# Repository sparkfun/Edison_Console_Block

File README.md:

Console
=====================

The Console expansion board delivers power to the Intel Edison while providing a simple console interface.  This is a minimal solution to get started using the Intel Edison.  The Console board can supply 4V and up to 1.5A of current to power the Edison and any other expansion boards you may add to your stack. This power is passed through the VSYS line of the Edison.

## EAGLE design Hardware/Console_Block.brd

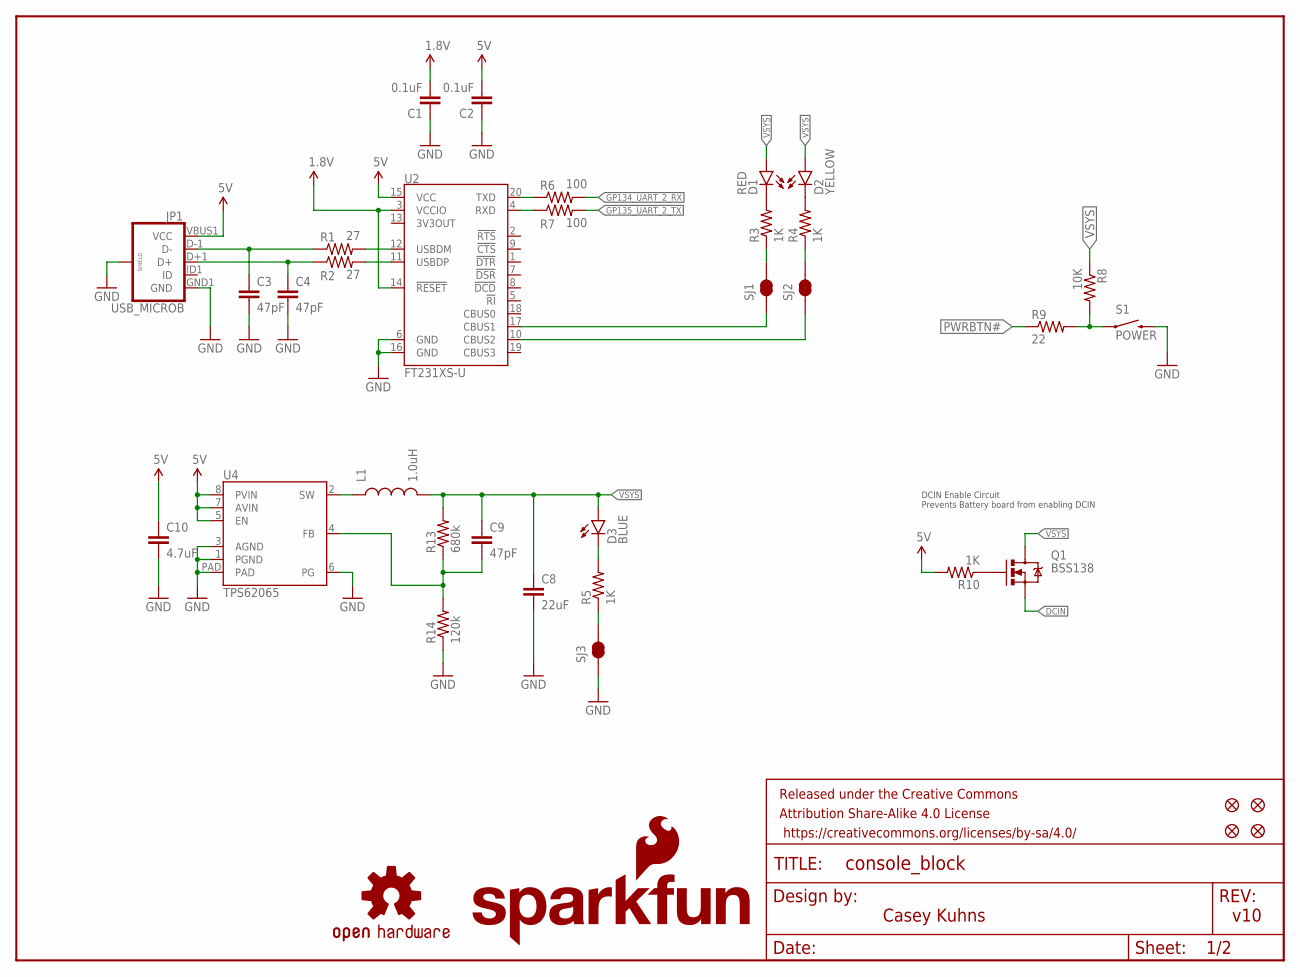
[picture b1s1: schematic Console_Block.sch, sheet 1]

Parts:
C1, C2: 0.1uF; 0603-CAP
C3, C4, C9: 47pF; 0603-CAP
C8: 22uF; 0805
C10: 4.7uF; 0603-CAP
D1: RED; LED-0603
D2: YELLOW; LED-0603
D3: BLUE; LED-0603
FID1, FID2, FID3, FID4: FIDUCIAL1X2; FIDUCIAL-1X2
FRAME1: FRAME-LETTER; CREATIVE_COMMONS
JP1: USB_MICROB; USB-B-MICRO-SMD_V03
L1: 1.0uH; INDUCTOR-SRP4020
LOGO1: SFE_LOGO_NAME_FLAME.1_INCH; SFE_LOGO_NAME_FLAME_.1
LOGO4: OSHW-LOGOS; OSHW-LOGO-S
Q1: BSS138; SOT23-3
R1, R2: 27; 0603
R3, R4, R5, R10: 1K; 0603-RES
R6, R7: 100; 0603-RES
R8: 10K; 0603-RES
R9: 22; 0603-RES
R13: 680k; 0603-RES
R14: 120k; 0603-RES
S1: POWER; TACTILE_SWITCH-SMD-RIGHT-ANGLE
SJ1, SJ2, SJ3: JUMPER-PAD-2-NC_BY_TRACE; PAD-JUMPER-2-NC_BY_TRACE_YES_SILK
U2: FT231XS-U; SSOP20_L
U4: TPS62065; WSON-8-PAD

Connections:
1.8V: C1.2, U2.3 (VCCIO), U2.14 (!RESET); also elsewhere on the board
5V: C2.2, C10.1, JP1.VBUS1 (VCC), R10.2, U2.15 (VCC), U4.5 (EN), U4.7 (AVIN), U4.8 (PVIN)
DCIN: Q1.2 (S); also elsewhere on the board
GND: C1.1, C2.1, C3.2, C4.2, C8.2, C10.2, JP1.GND1 (GND), JP1.SHIELD1 (SHIELD), JP1.SHIELD2 (SHIELD), JP1.SHIELD3 (SHIELD), R14.1, S1.2, SJ3.1, U2.6 (GND), U2.16 (GND), U4.1 (PGND), U4.3 (AGND), U4.6 (PG), U4.PAD; also elsewhere on the board
GP134_UART_2_RX: R6.2; also elsewhere on the board
GP135_UART_2_TX: R7.2; also elsewhere on the board
unnamed: SJ1.1, U2.17 (CBUS1)
unnamed: C3.1, JP1.D-1 (D-), R1.1
unnamed: C4.1, JP1.D+1 (D+), R2.1
unnamed: R1.2, U2.12 (USBDM)
unnamed: R2.2, U2.11 (USBDP)
unnamed: SJ2.1, U2.10 (CBUS2)
unnamed: R3.1, SJ1.2
unnamed: R4.1, SJ2.2
unnamed: D1.C, R3.2
unnamed: D2.C, R4.2
unnamed: R6.1, U2.20 (TXD)
unnamed: D3.C, R5.2
unnamed: R5.1, SJ3.2
unnamed: R7.1, U2.4 (RXD)
unnamed: R8.2, R9.2, S1.1
unnamed: Q1.1 (G), R10.1
unnamed: C9.2, R13.1, R14.2, U4.4 (FB)
unnamed: L1.P$1 (1), U4.2 (SW)
PWRBTN#: R9.1; also elsewhere on the board
VSYS: C8.1, C9.1, D1.A, D2.A, D3.A, L1.P$2 (2), Q1.3 (D), R8.1, R13.2; also elsewhere on the board

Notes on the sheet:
v10
Casey Kuhns
DCIN Enable Circuit Prevents Battery board from enabling DCIN

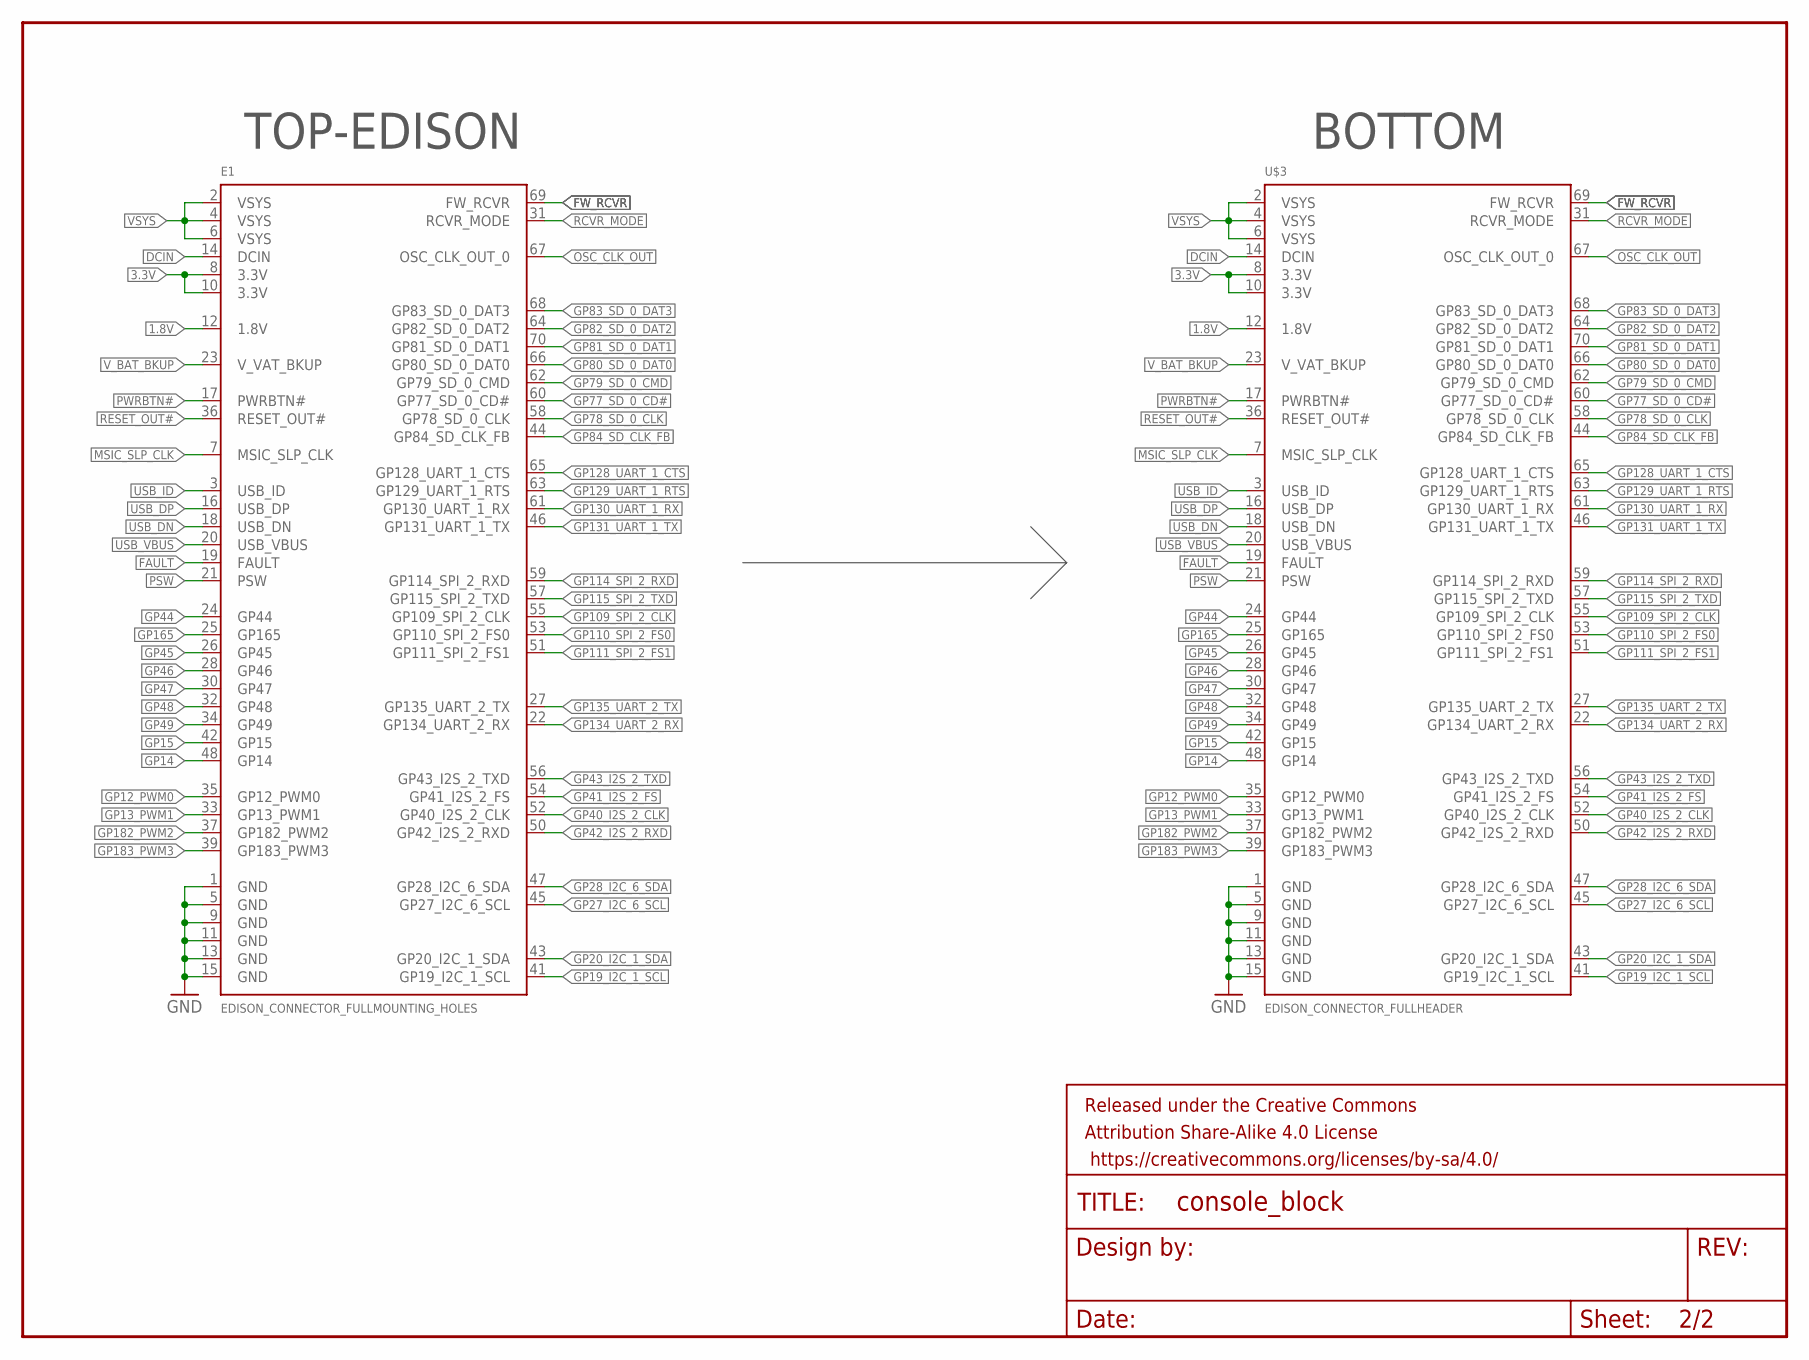
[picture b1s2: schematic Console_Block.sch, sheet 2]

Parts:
E1: EDISON_CONNECTOR_FULLMOUNTING_HOLES; EDISON_DAUGHTER
FRAME2: FRAME-LETTER; CREATIVE_COMMONS
U$3: EDISON_CONNECTOR_FULLHEADER; DF40C-70DP-0.4(51)

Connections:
1.8V: E1.12 (1.8V), U$3.12 (1.8V); also elsewhere on the board
3.3V: E1.8 (3.3V), E1.10 (3.3V), U$3.8 (3.3V), U$3.10 (3.3V)
DCIN: E1.14 (DCIN), U$3.14 (DCIN); also elsewhere on the board
FAULT: E1.19 (FAULT), U$3.19 (FAULT)
FW_RCVR: E1.69 (FW_RCVR), U$3.69 (FW_RCVR)
GND: E1.1 (GND), E1.5 (GND), E1.9 (GND), E1.11 (GND), E1.13 (GND), E1.15 (GND), U$3.1 (GND), U$3.5 (GND), U$3.9 (GND), U$3.11 (GND), U$3.13 (GND), U$3.15 (GND); also elsewhere on the board
GP12_PWM0: E1.35 (GP12_PWM0), U$3.35 (GP12_PWM0)
GP13_PWM1: E1.33 (GP13_PWM1), U$3.33 (GP13_PWM1)
GP14: E1.48 (GP14), U$3.48 (GP14)
GP15: E1.42 (GP15), U$3.42 (GP15)
GP19_I2C_1_SCL: E1.41 (GP19_I2C_1_SCL), U$3.41 (GP19_I2C_1_SCL)
GP20_I2C_1_SDA: E1.43 (GP20_I2C_1_SDA), U$3.43 (GP20_I2C_1_SDA)
GP27_I2C_6_SCL: E1.45 (GP27_I2C_6_SCL), U$3.45 (GP27_I2C_6_SCL)
GP28_I2C_6_SDA: E1.47 (GP28_I2C_6_SDA), U$3.47 (GP28_I2C_6_SDA)
GP40_I2S_2_CLK: E1.52 (GP40_I2S_2_CLK), U$3.52 (GP40_I2S_2_CLK)
GP41_I2S_2_FS: E1.54 (GP41_I2S_2_FS), U$3.54 (GP41_I2S_2_FS)
GP42_I2S_2_RXD: E1.50 (GP42_I2S_2_RXD), U$3.50 (GP42_I2S_2_RXD)
GP43_I2S_2_TXD: E1.56 (GP43_I2S_2_TXD), U$3.56 (GP43_I2S_2_TXD)
GP44: E1.24 (GP44), U$3.24 (GP44)
GP45: E1.26 (GP45), U$3.26 (GP45)
GP46: E1.28 (GP46), U$3.28 (GP46)
GP47: E1.30 (GP47), U$3.30 (GP47)
GP48: E1.32 (GP48), U$3.32 (GP48)
GP49: E1.34 (GP49), U$3.34 (GP49)
GP77_SD_0_CD#: E1.60 (GP77_SD_0_CD#), U$3.60 (GP77_SD_0_CD#)
GP78_SD_0_CLK: E1.58 (GP78_SD_0_CLK), U$3.58 (GP78_SD_0_CLK)
GP79_SD_0_CMD: E1.62 (GP79_SD_0_CMD), U$3.62 (GP79_SD_0_CMD)
GP80_SD_0_DAT0: E1.66 (GP80_SD_0_DAT0), U$3.66 (GP80_SD_0_DAT0)
GP81_SD_0_DAT1: E1.70 (GP81_SD_0_DAT1), U$3.70 (GP81_SD_0_DAT1)
GP82_SD_0_DAT2: E1.64 (GP82_SD_0_DAT2), U$3.64 (GP82_SD_0_DAT2)
GP83_SD_0_DAT3: E1.68 (GP83_SD_0_DAT3), U$3.68 (GP83_SD_0_DAT3)
GP84_SD_CLK_FB: E1.44 (GP84_SD_CLK_FB), U$3.44 (GP84_SD_CLK_FB)
GP109_SPI_2_CLK: E1.55 (GP109_SPI_2_CLK), U$3.55 (GP109_SPI_2_CLK)
GP110_SPI_2_FS0: E1.53 (GP110_SPI_2_FS0), U$3.53 (GP110_SPI_2_FS0)
GP111_SPI_2_FS1: E1.51 (GP111_SPI_2_FS1), U$3.51 (GP111_SPI_2_FS1)
GP114_SPI_2_RXD: E1.59 (GP114_SPI_2_RXD), U$3.59 (GP114_SPI_2_RXD)
GP115_SPI_2_TXD: E1.57 (GP115_SPI_2_TXD), U$3.57 (GP115_SPI_2_TXD)
GP128_UART_1_CTS: E1.65 (GP128_UART_1_CTS), U$3.65 (GP128_UART_1_CTS)
GP129_UART_1_RTS: E1.63 (GP129_UART_1_RTS), U$3.63 (GP129_UART_1_RTS)
GP130_UART_1_RX: E1.61 (GP130_UART_1_RX), U$3.61 (GP130_UART_1_RX)
GP131_UART_1_TX: E1.46 (GP131_UART_1_TX), U$3.46 (GP131_UART_1_TX)
GP134_UART_2_RX: E1.22 (GP134_UART_2_RX), U$3.22 (GP134_UART_2_RX); also elsewhere on the board
GP135_UART_2_TX: E1.27 (GP135_UART_2_TX), U$3.27 (GP135_UART_2_TX); also elsewhere on the board
GP165: E1.25 (GP165), U$3.25 (GP165)
GP182_PWM2: E1.37 (GP182_PWM2), U$3.37 (GP182_PWM2)
GP183_PWM3: E1.39 (GP183_PWM3), U$3.39 (GP183_PWM3)
MSIC_SLP_CLK: E1.7 (MSIC_SLP_CLK), U$3.7 (MSIC_SLP_CLK)
OSC_CLK_OUT: E1.67 (OSC_CLK_OUT_0), U$3.67 (OSC_CLK_OUT_0)
PSW: E1.21 (PSW), U$3.21 (PSW)
PWRBTN#: E1.17 (PWRBTN#), U$3.17 (PWRBTN#); also elsewhere on the board
RCVR_MODE: E1.31 (RCVR_MODE), U$3.31 (RCVR_MODE)
RESET_OUT#: E1.36 (RESET_OUT#), U$3.36 (RESET_OUT#)
USB_DN: E1.18 (USB_DN), U$3.18 (USB_DN)
USB_DP: E1.16 (USB_DP), U$3.16 (USB_DP)
USB_ID: E1.3 (USB_ID), U$3.3 (USB_ID)
USB_VBUS: E1.20 (USB_VBUS), U$3.20 (USB_VBUS)
VSYS: E1.2 (VSYS), E1.4 (VSYS), E1.6 (VSYS), U$3.2 (VSYS), U$3.4 (VSYS), U$3.6 (VSYS); also elsewhere on the board
V_BAT_BKUP: E1.23 (V_VAT_BKUP), U$3.23 (V_VAT_BKUP)

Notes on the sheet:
TOP-EDISON
BOTTOM

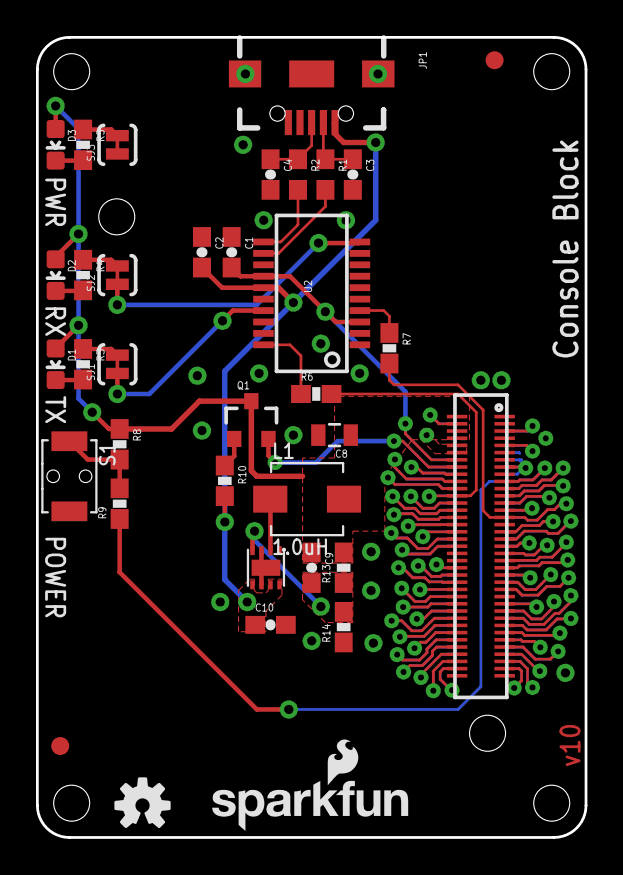
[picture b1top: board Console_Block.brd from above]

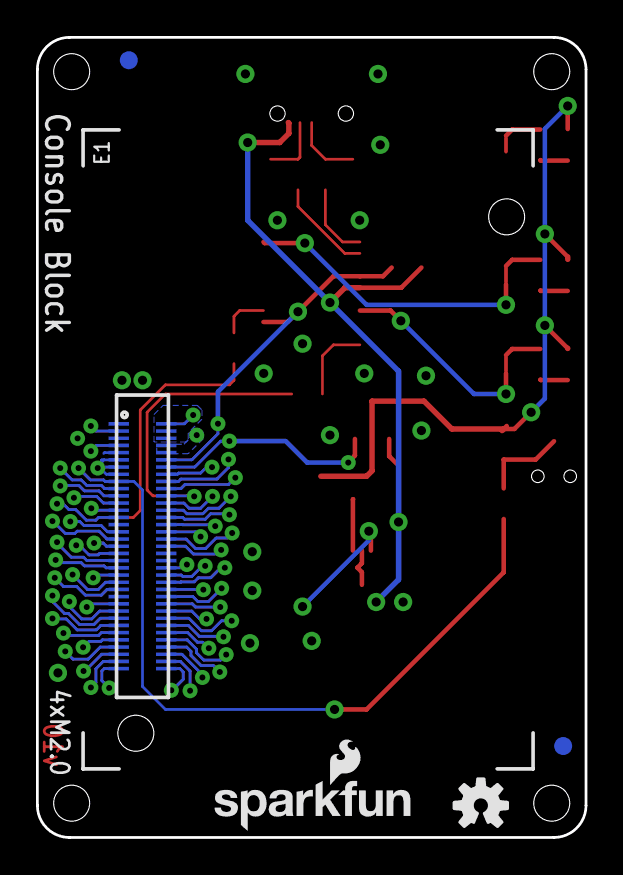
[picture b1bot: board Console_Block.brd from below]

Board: 2 copper layers, 30.5 x 44.5 mm, 43 parts (6 on the bottom side), 77 nets.

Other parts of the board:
LOGO2: OSHW-LOGOS; OSHW-LOGO-S
LOGO3: SFE_LOGO_NAME_FLAME.1_INCH; SFE_LOGO_NAME_FLAME_.1

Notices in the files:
parts and their libraries:
SparkFun-Aesthetics: Licensing: Creative Commons ShareAlike 4.0 International - https://creativecommons.org/licenses/by-sa/4.0
SparkFun-Aesthetics: Released under the Creative Commons Attribution Share-Alike 4.0 License
SparkFun-Aesthetics: https://creativecommons.org/licenses/by-sa/4.0
